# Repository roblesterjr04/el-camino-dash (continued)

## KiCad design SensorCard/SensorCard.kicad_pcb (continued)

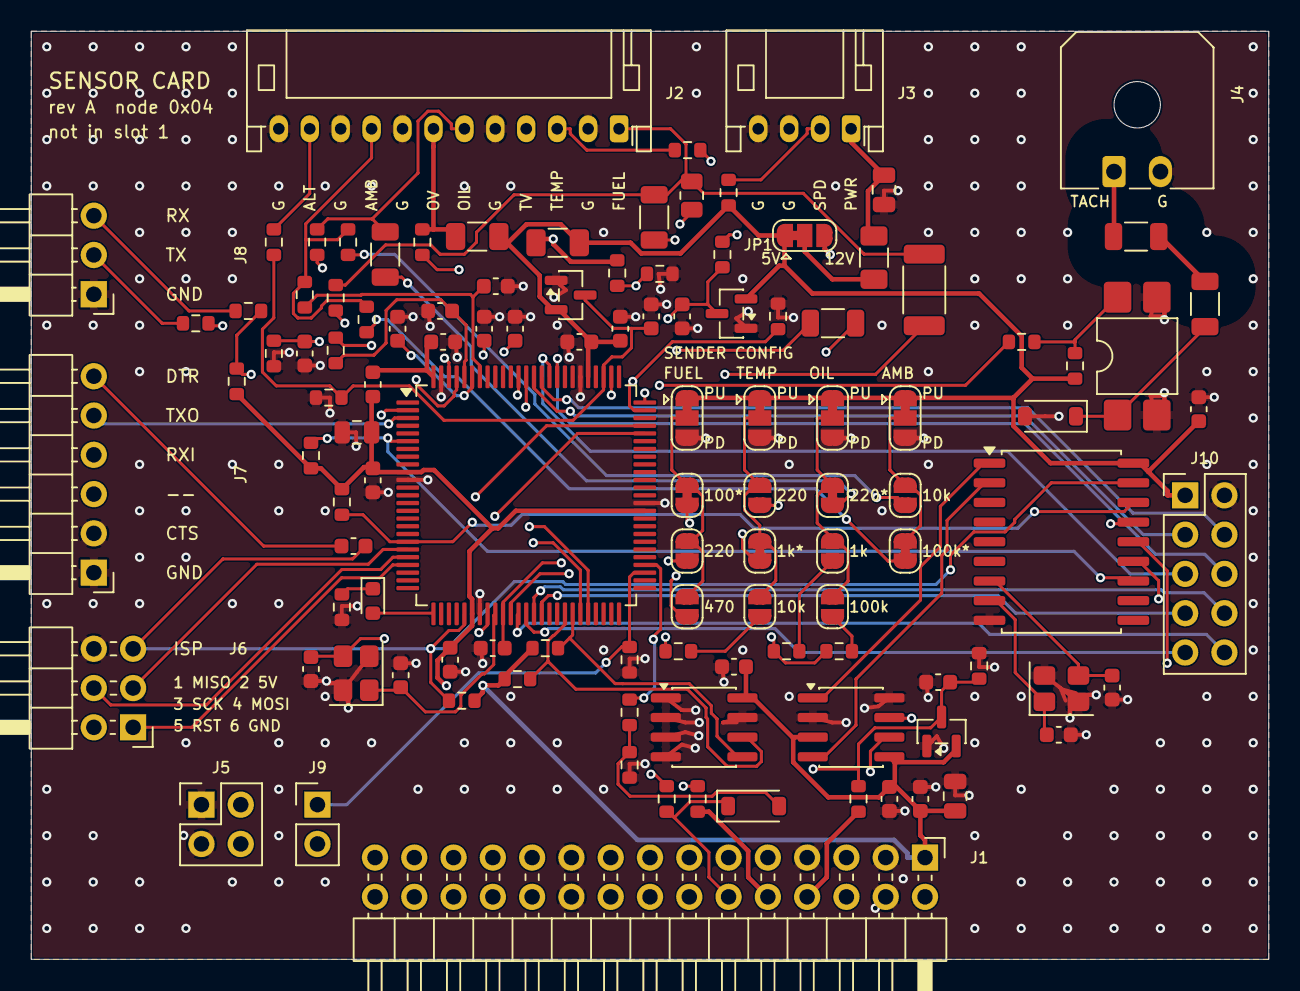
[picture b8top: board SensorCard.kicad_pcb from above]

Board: 4 copper layers, 80.0 x 60.0 mm, 114 parts (0 on the bottom side), 86 nets.

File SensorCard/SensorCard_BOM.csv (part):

Qty,Designators,Manufacturer part,Description,Package,Type,Side,Notes
1,U1,Microchip ATmega2560-16AU,"Sensor pack MCU. USART0 = FTDI header, USART1 = sensor frames (J8), SPI = MCP2515 + ISP, ICP4 / ICP5 = tach / speed",TQFP-100_14x14mm_P0.5mm,SMD,Top,Arrives blank: flash over J6 (ISP); fuses in DATASHEET.md
1,U2,Microchip MCP2515-I/SO,"CAN controller (node 0x04, fixed)",SOIC-18W_7.5x11.6mm_P1.27mm,SMD,Top,
1,U3,NXP TJA1051T/3/1J,"CAN transceiver, VIO 5 V, STBY low. No termination: a card never terminates the bus",SOIC-8_3.9x4.9mm_P1.27mm,SMD,Top,
1,U4,Fujitsu MB85RC256VPNF-G-JNERE1,"32 KB I2C FRAM, address 0x50: odometer (A / B slots with CRC-8). Lives on the card: set a new card's mileage in firmware",SOIC-8_3.9x4.9mm_P1.27mm,SMD,Top,
1,U5,Everlight EL817S1(C)(TU)-F,Tach isolation,SMDIP-4_W7.62mm,SMD,Top,LCSC C106900. Any PC817 in the 4-SMD gull wing
1,Y1,YXC X322516MOB4SI,"16 MHz, 3225, CL 12 pF (18p + 18p in series plus stray)",Crystal_SMD_3225-4Pin_3.2x2.5mm,SMD,Top,LCSC C12668. C12 / C13 18p give about 13-14 pF load (CL 12 pF part): fine
1,Y2,YXC X322516MOB4SI,"MCP2515 clock, own crystal",Crystal_SMD_3225-4Pin_3.2x2.5mm,SMD,Top,"LCSC C12668. C16 / C17 18p, as Y1"
1,J1,Sullins PRPC015DBAN-M71RC,"Right-angle 2x15 header on the bottom edge (the slot pinout, docs/hardware/accessory_ports.md). Used: 5 V, GND, CAN, switched 12 V (8), constant 12 V (10), WAKE (12). Not used: 3.3 V, slot ID (the node is fixed), LAMP, REV, I2S, audio, AUX 12 V",PinHeader_2x15_P2.54mm_Horizontal,THT,Top,"Same part as the audio and GPS cards; on the bottom edge, pins pointing off the board"
1,J2,JST S12B-PH-K-S,"Senders: 1 FUEL, 2 FUEL return, 3 ETEMP, 4 ETEMP V (5 V, 0.1 A PTC), 5 ETEMP return, 6 OILP, 7 OILP V (5 V, 0.1 A PTC), 8 OILP return, 9 AMB, 10 AMB return, 11 ALT L (alternator lamp terminal, 12 V level), 12 GND",JST_PH_S12B-PH-K_1x12_P2.00mm_Horizontal,THT,Top,
1,J3,JST S4B-PH-K-S,"Speed sensor: 1 sensor power (5 V or 12 V by JP1, 0.1 A PTC), 2 signal, 3 GND, 4 GND / shield",JST_PH_S4B-PH-K_1x04_P2.00mm_Horizontal,THT,Top,
1,J4,Molex 43650-0200,"Tach: 1 coil negative / HEI tach terminal / ignition box tach output, 2 GND",Molex_Micro-Fit_3.0_43650-0200_1x02_P3.00mm_Horizontal,THT,Top,
1,J5,XFCN PZ254V-12-4P,"RPM select jumpers (pulses per revolution; internal pull-ups): 1-2 = A, 3-4 = B",PinHeader_2x02_P2.54mm_Vertical,THT,Top,
1,J6,XFCN PZ254R-12-6P,ISP (USBasp or AVRISP mkII; USBtiny is unreliable above 128 KB). Pin 2 is the card 5 V: power the card from its slot,PinHeader_2x03_P2.54mm_Horizontal,THT,Top,
1,J7,Sullins PRPC006SBAN-M71RC,"FTDI 6-pin (5 V logic): 1 GND, 2 CTS (grounded), 3 VCC (not used: power from the slot), 4 adapter TX, 5 adapter RX, 6 DTR",PinHeader_1x06_P2.54mm_Horizontal,THT,Top,
1,J8,Sullins PREC003SBAN-M71RC,"Sensor serial (USART1, 5 V, 115200 8N1): 1 GND, 2 TX (sensor frames out: jumper wire to the main board J27 pin 1), 3 RX (in; unused in the car)",PinHeader_1x03_P2.54mm_Horizontal,THT,Top,
1,J9,Sullins PRPC002SAAN-RC,"Demo jumper: fitted = the sensor pack sends a fake sweep (bench only). 1 DEMO, 2 +5V",PinHeader_1x02_P2.54mm_Vertical,THT,Top,"Plus one 2.54 mm jumper shunt (Sullins QPC02SXGN-RC), not fitted: bench only"
1,J10,XFCN PZ254V-12-10P,"Spare 2560 pins: ADC10-13 (port K: analog or digital, pin-change interrupts), D44-D47 (PWM). 5 V logic, no protection",PinHeader_2x05_P2.54mm_Vertical,THT,Top,
1,JP1,"(PCB solder jumper, no part)",Speed sensor supply: 1-2 (bridged as delivered) = 5 V; cut 1-2 and bridge 2-3 = slot switched 12 V,SolderJumper-3_P1.3mm_Bridged12_RoundedPad1.0x1.5mm,SMD,Top,Bridged as delivered
1,JP2,"(PCB solder jumper, no part)",FUEL topology: 1-2 (bridged as delivered) = pull-up to +5 V; cut 1-2 and bridge 2-3 = pull-down to GND,SolderJumper-3_P1.3mm_Bridged12_RoundedPad1.0x1.5mm,SMD,Top,Bridged as delivered
1,JP3,"(PCB solder jumper, no part)",ETEMP topology: 1-2 (bridged as delivered) = pull-up to +5 V; cut 1-2 and bridge 2-3 = pull-down to GND,SolderJumper-3_P1.3mm_Bridged12_RoundedPad1.0x1.5mm,SMD,Top,Bridged as delivered
1,JP4,"(PCB solder jumper, no part)",OILP topology: 1-2 (bridged as delivered) = pull-up to +5 V; cut 1-2 and bridge 2-3 = pull-down to GND,SolderJumper-3_P1.3mm_Bridged12_RoundedPad1.0x1.5mm,SMD,Top,Bridged as delivered
1,JP5,"(PCB solder jumper, no part)",AMB topology: 1-2 (bridged as delivered) = pull-up to +5 V; cut 1-2 and bridge 2-3 = pull-down to GND,SolderJumper-3_P1.3mm_Bridged12_RoundedPad1.0x1.5mm,SMD,Top,Bridged as delivered
1,JP6,"(PCB solder jumper, no part)",FUEL 100 select: bridged as delivered,SolderJumper-2_P1.3mm_Bridged_RoundedPad1.0x1.5mm,SMD,Top,Bridged as delivered
1,JP7,"(PCB solder jumper, no part)",FUEL 220 select: open as delivered,SolderJumper-2_P1.3mm_Open_RoundedPad1.0x1.5mm,SMD,Top,Open as delivered
1,JP8,"(PCB solder jumper, no part)",FUEL 470 select: open as delivered,SolderJumper-2_P1.3mm_Open_RoundedPad1.0x1.5mm,SMD,Top,Open as delivered
1,JP9,"(PCB solder jumper, no part)",ETEMP 220 select: open as delivered,SolderJumper-2_P1.3mm_Open_RoundedPad1.0x1.5mm,SMD,Top,Open as delivered
1,JP10,"(PCB solder jumper, no part)",ETEMP 1k select: bridged as delivered,SolderJumper-2_P1.3mm_Bridged_RoundedPad1.0x1.5mm,SMD,Top,Bridged as delivered
1,JP11,"(PCB solder jumper, no part)",ETEMP 10k select: open as delivered,SolderJumper-2_P1.3mm_Open_RoundedPad1.0x1.5mm,SMD,Top,Open as delivered
1,JP12,"(PCB solder jumper, no part)",OILP 220 select: bridged as delivered,SolderJumper-2_P1.3mm_Bridged_RoundedPad1.0x1.5mm,SMD,Top,Bridged as delivered
1,JP13,"(PCB solder jumper, no part)",OILP 1k select: open as delivered,SolderJumper-2_P1.3mm_Open_RoundedPad1.0x1.5mm,SMD,Top,Open as delivered
1,JP14,"(PCB solder jumper, no part)",OILP 100k select: open as delivered,SolderJumper-2_P1.3mm_Open_RoundedPad1.0x1.5mm,SMD,Top,Open as delivered
1,JP15,"(PCB solder jumper, no part)",AMB 10k select: open as delivered,SolderJumper-2_P1.3mm_Open_RoundedPad1.0x1.5mm,SMD,Top,Open as delivered
1,JP16,"(PCB solder jumper, no part)",AMB 100k select: bridged as delivered,SolderJumper-2_P1.3mm_Bridged_RoundedPad1.0x1.5mm,SMD,Top,Bridged as delivered
3,D1 D4 D5,"Nexperia BAT54S,215","Input clamps to GND / 5 V (ignition sense, alternator L, speed)",SOT-23,SMD,Top,
1,D2,Vishay BAT42W-E3-08,"Hold diode: this card can only drive WAKE high, never load it (other cards drive it too)",D_SOD-123,SMD,Top,
1,D3,Lite-On LTST-C191KGKT,"Status (PB7, Arduino D13)",0603,SMD,Top,
1,D6,Diodes Inc 1N4148W-7-F,Reverse clamp across the LED (coil kickback),D_SOD-123,SMD,Top,
1,FB1,Murata BLM18KG601SN1D,AVCC filter,0603,SMD,Top,
3,F1 F2 F3,Littelfuse 1206L010/60WR,"0.1 A, 60 V feed fuses, 1206: ETEMP V, OILP V, speed sensor power",1206,SMD,Top,
1,R1,Yageo RC0603FR-0715KL,Ignition sense divider top (from the slot switched 12 V),0603,SMD,Top,
18,R2 R6 R8 R10 R11 R12 R17 R19 R21 R27 R31 R33 R34 R35 R36 R38 R39 R40,Yageo RC0603FR-0710KL,10k resistor,0603,SMD,Top,
3,R3 R30 R32,Yageo RC0603FR-07100KL,100k resistor,0603,SMD,Top,
3,R4 R37 R43,Yageo RC0603FR-0722KL,22k resistor,0603,SMD,Top,
3,R5 R13 R14,Yageo RC0603FR-074K7L,4.7k resistor,0603,SMD,Top,
1,R7,Yageo RC0603FR-0747KL,WAKE into the 2560 (series: the line may be up while the 2560 is unpowered),0603,SMD,Top,
7,R9 R16 R18 R20 R26 R29 R44,Yageo RC0603FR-071KL,1k resistor,0603,SMD,Top,
1,R15,Yageo RC0603FR-07100RL,Series R on the serial out (a wire leaves the card),0603,SMD,Top,
1,R22,Yageo RC2010FK-07100RL,"FUEL bank, 100: 0-30R senders (the factory 1964 GM sender); 2010 for 0.25 W into a shorted sender",2010,SMD,Top,Sender bias bank: selected by a solder jumper
3,R23 R25 R28,Yageo RC1206FR-07220RL,220 resistor,1206,SMD,Top,
1,R24,Yageo RC0805FR-07470RL,"FUEL bank, 470: 240-33R senders",0805,SMD,Top,Sender bias bank: selected by a solder jumper
2,R41 R42,Yageo RC1206FR-074K7L,4.7k resistor,1206,SMD,Top,
2,C1 C9,Samsung CL21B106KOQNNNE,10u capacitor,0805,SMD,Top,
14,C2 C3 C4 C5 C6 C7 C8 C10 C11 C14 C15 C18 C19 C24,Samsung CL10B104KB8NNNC,100n capacitor,0603,SMD,Top,
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
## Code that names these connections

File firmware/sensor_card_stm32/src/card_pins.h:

#pragma once

// The rev B card's pins (SensorCard2/README.md, pin map): STM32G0B1KBU6, UFQFPN-32. Names are the STM32duino port
// pin names (PA0 ...), which the generic variant defines as Arduino pin numbers.
#include <Arduino.h>
#include <stdint.h>

static const uint32_t PIN_LED = PB5;         // status LED, high = on
static const uint32_t PIN_PWR_HOLD = PA15;   // drives WAKE through D1 to hold the main board's 5 V rail
static const uint32_t PIN_RPM_SEL_A = PC6;   // J5 1-2, low = fitted (internal pull-up)
static const uint32_t PIN_RPM_SEL_B = PB3;   // J5 3-4, low = fitted (internal pull-up)
static const uint32_t PIN_TEMP_MON = PB2;    // ETEMP V feed present (10k / 15k from the 5 V feed), high = OK
static const uint32_t PIN_PRESS_MON = PB9;   // OILP V feed present, high = OK
static const uint32_t PIN_TACH = PA8;        // TIM1_CH1 (AF2), falling edge = spark (the opto pulls it low)
static const uint32_t PIN_SPEED = PB4;       // TIM3_CH1 (AF1), falling edge
static const uint32_t PIN_J8_TX = PA2;       // USART2: the sensor frames out (through U7 to 5 V)
static const uint32_t PIN_J8_RX = PA3;
static const uint32_t PIN_FRAM_SDA = PB7;    // I2C1
static const uint32_t PIN_FRAM_SCL = PB6;
// USART1 (PA9 / PA10, J7) is `Serial`: SERIAL_UART_INSTANCE / PIN_SERIAL_* in platformio.ini.
// FDCAN1 is PA11 (RX) / PA12 (TX), AF3: hw_fdcan.cpp. SWD is PA13 / PA14 (J6).

// ADC1 inputs (hw_adc.cpp scans them in this, ascending, order)
static const uint8_t ADC_FUEL = 0, ADC_TEMP = 1, ADC_OIL = 4, ADC_AMB = 5, ADC_ALT = 6, ADC_BATT = 7, ADC_WAKE = 8,
                     ADC_IGN = 9;

// The level inputs' dividers (top / bottom, kohm) and the slot voltages they switch at, the same as rev A's
static const float kIgnDivTop = 33.0f, kIgnDivBottom = 10.0f, kIgnOnVolts = 7.5f, kIgnOffVolts = 3.75f;
static const float kAltDivTop = 39.0f, kAltDivBottom = 10.0f, kAltOnVolts = 9.6f, kAltOffVolts = 4.8f;
static const float kBattDivTop = 100.0f, kBattDivBottom = 22.0f;

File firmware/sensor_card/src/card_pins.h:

#pragma once

// The sensor card's pins (SensorCard/DATASHEET.md, MCU pin map). They are the ATmega2560's pins numbered the way an
// Arduino Mega 2560 numbers them, so the same image runs on a Mega on the bench.
#include <stdint.h>

static const uint8_t PIN_CAN_CS = 53;      // PB0 (SS): MCP2515 chip select on the card
static const uint8_t PIN_CAN_INT = 2;      // PE4 (INT4): MCP2515 INT (the driver polls; it is not needed)
static const uint8_t PIN_LED = 13;         // PB7: status LED, high = on
static const uint8_t PIN_TACH = 49;        // PL0 ICP4: tach, falling edge = spark
static const uint8_t PIN_SPEED = 48;       // PL1 ICP5: speed, falling edge
static const uint8_t PIN_DEMO = 37;        // PC0: J9, high = demo sweep (10k pull-down on the card)
static const uint8_t PIN_PWR_HOLD = 36;    // PC1: drives WAKE to hold the main board's 5 V rail
static const uint8_t PIN_RPM_SEL_B = 29;   // PA7: J5 3-4, low = fitted
static const uint8_t PIN_RPM_SEL_A = 28;   // PA6: J5 1-2, low = fitted
static const uint8_t PIN_PRESS_MON = 26;   // PA4: OILP V feed monitor, high = OK
static const uint8_t PIN_TEMP_MON = 25;    // PA3: ETEMP V feed monitor, high = OK
static const uint8_t PIN_IGN = 23;         // PA1: ignition (slot switched 12 V), high = on
static const uint8_t PIN_ALT_L = 22;       // PA0: alternator L, high = charging

// ADC channels
static const uint8_t ADC_FUEL = 0, ADC_TEMP = 1, ADC_OIL = 2, ADC_AMB = 3, ADC_BATT = 8, ADC_WAKE = 9;

// MCP2515 chip-select candidates, tried in this order when none is set: the card's own, then the ones CAN shields use
static const uint8_t kCsCandidates[3] = {53, 10, 9};

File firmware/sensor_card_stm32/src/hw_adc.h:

#pragma once
#include <stdint.h>

// ADC1 scanning the eight inputs (PA0 PA1 PA4 PA5 PA6 PA7 PB0 PB1 = IN0 1 4 5 6 7 8 9) by DMA into a ring of the last
// 32 scans, hardware-oversampled 16x, so nothing ever blocks on a conversion and no interrupt runs: one scan is about
// 1.4 ms, the ring about 44 ms, and take() averages what is in it. Counts come back on rev A's 10-bit scale
// (adc_scale.h), which is what the calibration and the screens expect.
enum AdcSlot : uint8_t { SLOT_FUEL, SLOT_TEMP, SLOT_OIL, SLOT_AMB, SLOT_ALT, SLOT_BATT, SLOT_WAKE, SLOT_IGN, SLOT_COUNT };

void adc_begin();
/** The slot's average over the ring, on rev A's scale (senders and WAKE: 0..1023 ratiometric; battery: rescaled to
 *  the 5 V reference; ALT / IGN: 0..1023 of 3.3 V). False until the first scan has landed. */
bool adc_take(AdcSlot s, float *avg);
/** The latest 12-bit sample of a slot (for `adc`). */
uint16_t adc_raw12(AdcSlot s);
/** The level inputs through their dividers with hysteresis: ignition on, alternator L high. */
bool adc_ign_on();
bool adc_alt_high();

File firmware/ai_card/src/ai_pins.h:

#pragma once

// ESP32-S3-WROOM-1U-N16R8 pins on the AI card (AICard/generate/gen_sch.py is the source of truth; keep both in step).
// Not used: GPIO0 (BOOT only), 3, 45, 46 (strapping), 26-37 (flash and octal PSRAM), 19 / 20 (native USB).

#define AI_PIN_CAN_TX 9
#define AI_PIN_CAN_RX 10
#define AI_PIN_SLOT_ID 4        // ADC1_CH3: 10k to 3.3 V on the card, the slot's resistor to GND
#define AI_PIN_AUX_SENSE 5      // ADC1_CH4: AUX 12 V through 220k / 47k (2.1 V at 12 V): the buck's INPUT, since the buck waits for it
#define AI_PIN_NTC 8            // ADC1_CH7: 10k NTC (beta 3950) to GND, 10k to 3.3 V
#define AI_PIN_I2S_BCK 6        // rail BCK in (slave)
#define AI_PIN_I2S_WS 7         // rail WS in
#define AI_PIN_I2S_MIC 15       // rail MIC in (the audio card's PCM1808 data)
#define AI_PIN_I2S_RET 16       // RET data out, to the 74LVC125
#define AI_PIN_RET_OE_N 17      // 74LVC125 /OE: low = the buffer drives RET. 100k pull-up on the card: off at power-up
#define AI_PIN_LINK_TX 41       // UART1 TX -> module RXD (header pin 10), 1k in series
#define AI_PIN_LINK_RX 42       // UART1 RX <- module TXD (header pin 8), 1k in series
#define AI_PIN_BUCK_EN 11       // high enables the module's 5 V buck (NMOS pulls the buck's EN low otherwise)
#define AI_PIN_SHUTDOWN_REQ 12  // -> module header pin 31 (GPIO6), 1k in series, 100k pull-down
#define AI_PIN_ALIVE 13         // <- module header pin 29 (GPIO5), 1k in series, 100k pull-down
#define AI_PIN_ATTN 14          // spare, module header pin 33, input
#define AI_PIN_LED_MODULE 1     // green: module running
#define AI_PIN_LED_MIC 2        // amber: the microphone is open (listening)
// GPIO43 / 44 are the debug UART (J5), 19 / 20 the USB-C.

#define AI_NTC_R_FIXED 10000
#define AI_NTC_R0 10000
#define AI_NTC_BETA 3950
#define AI_AUX_PRESENT_MV 1000  // above this AUX 12 V is up (about 6.4 V at the 220k / 47k divider: 17.6 % of the input)

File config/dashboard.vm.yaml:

system:
  mode: simulation
  log_level: DEBUG
  target_fps: 30
  window_title: El Camino Dash (VM)
  display_render_mode: multi_window
  keyboard_focus_control_only: true
  startup_sweep_enabled: true
  startup_sweep_up_s: 1.1
  startup_sweep_hold_s: 0.12
  startup_sweep_down_s: 0.7
  left_to_right_preview: false
  left_to_right_spacing_px: 16
  menu_schema_path: config/menu_schema.yaml
  odometer_start_miles: 12345.0
  odometer_persist_enabled: true
  odometer_state_path: data/odometer_state.vm.json
  odometer_write_interval_s: 1.5
  map_view_visible: false
  map_display_id: gauge_right
  simulation_map_image_path: assets/maps/testmap.png
  # Keep VM theme pinned unless manually changed in config.
  theme_persist_enabled: false
  theme_state_path: data/theme_state.vm.json
  raw_input_log_enabled: true
  raw_input_log_path: data/raw_inputs.vm.log
  raw_input_log_interval_s: 0.2

displays:
  - id: gauge_left
    enabled: true
    shape: round
    width: 1080
    height: 1080
    position: [0, 0]
    monitor_index: 0
    windowed: true
    fullscreen: false
    fps: 30
    role: gauge
    gauge_id: speedometer
  - id: gauge_center
    enabled: true
    shape: round
    width: 720
    height: 720
    position: [1080, 0]
    monitor_index: 1
    windowed: true
    fullscreen: false
    fps: 30
    role: gauge
    gauge_id: fuel
  - id: gauge_right
    enabled: true
    shape: round
    width: 1080
    height: 1080
    position: [540, 0]
    monitor_index: 2
    windowed: true
    fullscreen: false
    fps: 30
    role: gauge
    gauge_id: tachometer
  - id: control_rect
    enabled: true
    shape: rectangle
    width: 1050
    height: 600
    position: [0, 540]
    monitor_index: 3
    windowed: true
    fullscreen: false
    fps: 30
    role: control

themes:
  active: default
  allow_fallback: true
  theme_root: themes
  gauge_asset_root: assets/gauges
  font_name: freesansbold.ttf

gauges:
  speedometer: {label: Speed, unit: mph, source: speed_sensor.vehicle_speed, min_value: 0, max_value: 140, smoothing_alpha: 0.2, odometer_source: vehicle.odometer_miles, odometer_label: ODO, odometer_unit: mi, odometer_decimals: 1}
  tachometer: {label: RPM, unit: rpm, source: analog_inputs.engine_rpm, min_value: 0, max_value: 6000, smoothing_alpha: 0.2, secondary_label: Temp, secondary_source: analog_inputs.coolant_temp, secondary_unit: "F"}
  tsps: {label: TSPS, unit: "%", source: analog_inputs.fuel_level, min_value: 0, max_value: 100, smoothing_alpha: 0.3}
  fuel: {label: Fuel, unit: "%", source: analog_inputs.fuel_level, min_value: 0, max_value: 100, smoothing_alpha: 0.3}
  temp: {label: Temp, unit: "F", source: analog_inputs.coolant_temp, min_value: 40, max_value: 250, smoothing_alpha: 0.2}
  amp: {label: Amp, unit: A, source: analog_inputs.system_amp, min_value: -100, max_value: 100, smoothing_alpha: 0.2}
  oil: {label: Oil, unit: "psi", source: analog_inputs.oil_pressure, min_value: 0, max_value: 60, smoothing_alpha: 0.3}

inputs:
  rotary_encoders:
    - {id: menu, enabled: false, pin_a: 17, pin_b: 27, pin_button: 22, pull_up: true, debounce_ms: 3, invert_direction: false, acceleration: 1.0}
    - {id: aux, enabled: false, pin_a: 23, pin_b: 24, pin_button: 25, pull_up: true, debounce_ms: 3, invert_direction: false, acceleration: 1.0}
  analog_inputs:
    - {id: engine_rpm, enabled: false, adc_type: mcp3008, spi_bus: 0, spi_device: 0, channel: 0, min_raw: 0, max_raw: 1023, scale_min: 0, scale_max: 8000}
    - {id: fuel_level, enabled: false, adc_type: mcp3008, spi_bus: 0, spi_device: 0, channel: 1, min_raw: 0, max_raw: 1023, scale_min: 0, scale_max: 100}
    - {id: coolant_temp, enabled: false, adc_type: mcp3008, spi_bus: 0, spi_device: 0, channel: 2, min_raw: 0, max_raw: 1023, scale_min: 100, scale_max: 260}
    - {id: system_amp, enabled: false, adc_type: mcp3008, spi_bus: 0, spi_device: 0, channel: 3, min_raw: 0, max_raw: 1023, scale_min: -100, scale_max: 100}
  speed_sensors:
    - {id: vehicle_speed, enabled: false, gpio_pin: 5, pulses_per_revolution: 20, wheel_circumference_m: 2.1, timeout_ms: 800, smoothing_alpha: 0.35}
  simulated_data:
    enabled: false
    speed_period_s: 8.0
    rpm_period_s: 3.0
    fuel_period_s: 24.0
    temp_period_s: 14.0
    amp_period_s: 5.0
    oil_period_s: 9.0
    speed_range: [0, 95]
    rpm_range: [800, 6000]
    fuel_range: [0, 100]
    temp_range: [40, 250]
    amp_range: [-35, 60]
    oil_range: [8, 62]
  keyboard_sim:
    enabled: true
    rotate_repeat_ms: 130
    rpm_max: 10000
    temp_min: 40
    temp_max: 250
    amp_min: -100
    amp_max: 100
    oil_min: 0
    oil_max: 60
    mappings:
      menu_rotate_left: K_LEFT
      menu_rotate_right: K_RIGHT
      menu_press: K_RETURN
      aux_rotate_left: K_COMMA
      aux_rotate_right: K_PERIOD
      aux_press: K_SLASH
      speed_up: K_w
      speed_down: K_s
      rpm_up: K_e
      rpm_down: K_d
      fuel_up: K_r
      fuel_down: K_f
      temp_up: K_t
      temp_down: K_g
      amp_up: K_y
      amp_down: K_h
      oil_up: K_u
      oil_down: K_j

integrations:
  navit: {enabled: false, executable: navit, args: []}
  media: {enabled: false, music_root: media, startup_track: "", startup_volume: 0.5}
  bluetooth_metadata: {enabled: false, provider: mock}

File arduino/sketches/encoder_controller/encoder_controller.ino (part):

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// - UART1 TX=GP0, RX=GP1 (Pi link @115200)
// - SPI0 SCK=GP18, MOSI=GP19, MISO=GP16
static const uint8_t PIN_IR_RECEIVE = 22;
static const uint8_t OLED_CS = 17;
static const uint8_t OLED_DC = 20;
static const uint8_t OLED_RST = 21;
static const uint8_t UART_TX_PIN = 0;
static const uint8_t UART_RX_PIN = 1;
static const uint8_t OLED_SPI_SCK = 18;
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// IR demodulator OUT (active-low bursts; module usually has weak pull-up). Analog pin as digital in.
static const uint8_t PIN_IR_RECEIVE = A0;
// --- SPI OLED (SSD1322 256x64). HW SPI: MOSI=11, SCK=13 ---
static const uint8_t OLED_CS = 10;
// DC must go to the module's D/C pin; do not swap with RST — wrong wiring shows snow/garbage.
static const uint8_t OLED_DC = A4;
static const uint8_t OLED_RST = A5;
#define ELC_LINK_SERIAL Serial
#endif

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}

static void pulseOledReset() {
  pinMode(OLED_RST, OUTPUT);
  digitalWrite(OLED_RST, LOW);
  delay(10);
  digitalWrite(OLED_RST, HIGH);
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  SPI.setRX(OLED_SPI_MISO);
#endif
  SPI.begin();
  pinMode(OLED_CS, OUTPUT);
  digitalWrite(OLED_CS, HIGH);
  pinMode(OLED_DC, OUTPUT);
  pulseOledReset();

  linkBothPrint(F("OLED driver: "));
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
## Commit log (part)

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2026-02-27 Update README and configuration files for enhanced display mode support and installation scripts
    - Updated README.md to include detailed instructions for VM and hardware display modes, including new scripts for running in different environments.
    - Modified dashboard.dev.yaml and dashboard.vehicle.yaml to include new display settings such as `monitor_index`, `windowed`, and `fullscreen`.
    - Enhanced install_app.sh and install_pi_base.sh scripts to support virtual environment creation and installation with Xvfb.
    - Added new command-line arguments for display and render modes in main.py.
    - Improved error handling and configuration validation in the application.
    - Updated input manager to manage
2026-03-02 Refactor configuration and remove VM support scripts
    - Updated README.md to reflect changes in display definitions and removed references to VM-specific configurations.
    - Removed dashboard.vm.yaml and associated scripts for VM autostart and Xvfb support.
    - Adjusted dashboard.dev.yaml and dashboard.vehicle.yaml to streamline display settings, including the removal of the control display.
    - Enhanced main.py to support headless operation and updated display mode handling.
    - Improved validation in config.py to enforce display role requirements and added support for SPI display configurations.
    - Updated input management and signal handling in app.py for better shutdown behavior.
2026-03-02 Enhance installation script and configuration for display modes
    - Updated install.sh to include command-line options for skipping package installation and syncing, as well as specifying display modes and boot splash settings.
    - Added support for SPI and HDMI service files, improving flexibility for different display configurations.
    - Enhanced README.md with detailed installation steps for HDMI display setup and Bluetooth audio integration.
    - Updated requirements.txt to conditionally include RPi.GPIO and spidev for ARM platforms.
    - Improved validation in config.py to support new Bluetooth audio settings and turn signal configurations.
    - Refactored input handling in keyboard_sim.py to manage t
2026-03-04 Enhance installation script and configuration for Arduino integration
    - Updated install.sh to include new command-line options for Arduino firmware compilation and upload, allowing for better integration with Arduino devices.
    - Added functions for detecting Arduino serial ports and managing Arduino settings, including baud rate and GPIO configurations.
    - Enhanced README.md with instructions for Arduino sketch setup and flashing process.
    - Updated requirements.txt to include additional dependencies for Arduino communication.
    - Improved validation in config.py to support new Arduino serial configurations and fault simulation settings.
    - Refactored app.py to manage Arduino fault states and inte
2026-03-16 Archive legacy installation scripts and transition to image-first provisioning
    - Updated install.sh to inform users of the new image-first workflow using rpi-image-gen, removing legacy install logic.
    - Enhanced README.md to reflect the new provisioning process and updated deployment instructions for day-to-day development.
    - Added support for IR protocol configuration in dashboard YAML files, allowing for better integration with IR remote controls.
    - Improved deploy_to_pi.sh with new command-line options for service management and Python dependency updates.
    - Refactored configuration validation in config.py to support new IR remote settings.
    - Various updates to dashboard configuration files
2026-03-17 Update configuration and code for improved functionality and organization
    - Added new ambient temperature thermistor support in sensor_pack.ino, including pin definitions and reading logic.
    - Enhanced Arduino serial communication with a handshake mechanism to improve reliability.
    - Updated gauge-cluster-hdmi.service to streamline service startup and removed unnecessary dependencies on graphical targets.
    - Refined power_control_listener.py to include a startup ignore period for more stable operation during boot.
    - Adjusted dashboard configuration files to reflect changes in device layers and user permissions.
    - Improved installation scripts to support new command-line options and configuratio
2026-03-19 Update installation scripts and configuration for improved logging and Arduino integration
    - Enhanced install.sh to include detailed logging for service starts and errors, improving troubleshooting capabilities.
    - Updated Arduino serial port configurations across multiple dashboard YAML files to use /dev/ttyAMA3 for consistency.
    - Added new user group permissions in install.sh to ensure proper access for input devices.
    - Improved README.md with additional details on raw scancode mapping for IR remotes.
    - Refined wiring pinout documentation to clarify changes in UART and SPI configurations.
    - Various updates to ensure better integration and performance across the dashboard application.
2026-03-19 Update systemd installation script to manage gauge-power-control service
    - Added symlink for gauge-power-control.service to multi-user.target.wants.
    - Removed unnecessary cleanup of gauge-power-control.service from graphical targets.
    - Simplified comments regarding the power-control unit's default disabled state.
    - Ensured proper organization of service files for improved systemd management.
2026-03-23 Refactor wiring pinout and configuration for improved Arduino integration
    - Updated wiring pinout documentation to reflect changes in I2C and UART configurations for sensor-pack and encoder Arduino.
    - Disabled MCP23017 controls in dashboard configuration files, transitioning to dedicated encoder Arduino serial input.
    - Standardized serial port paths across multiple dashboard YAML files to use /dev/serial0 and /dev/ttyAMA4.
    - Enhanced installation scripts to support new command-line options for Arduino firmware management and improved logging.
    - Introduced new menu options for Wi-Fi management in menu schema, enhancing user interface functionality.
    - Various updates to ensure better integrati
2026-03-23 Remove legacy install.sh script and update documentation for new image-first workflow
    - Deleted the install.sh script as the project transitions to an image-first workflow using rpi-image-gen.
    - Updated WIRING_PINOUT.md to reflect changes in wiring configurations for IR and UART connections.
    - Enhanced Arduino-related documentation in README.md to include new installation and upload scripts.
    - Improved compile and upload scripts for Arduino to ensure better integration and functionality.
    - Updated dashboard configuration files to align with the new architecture and remove deprecated settings.
    - Various improvements to ensure consistency and clarity across documentation and configuration file
2026-04-01 Update wiring and configuration for improved Arduino integration and documentation
    - Added freetype-py to requirements.txt for enhanced font rendering.
    - Updated WIRING_PINOUT.md to clarify HDMI-first vehicle UI and UART connections for encoder and sensor pack.
    - Refined Arduino-related documentation in README.md to include new installation and upload scripts for RP2040.
    - Standardized serial port paths in dashboard configuration files to use /dev/ttyAMA1 and /dev/ttyAMA4.
    - Adjusted dashboard YAML files to disable legacy I2C configurations and enable Arduino serial communication.
    - Enhanced menu schema to include new options for Bluetooth and improved user interface functionality.
2026-04-01 HDMI: dual-head X11 extended option, Pi image hooks, hdmi5 layout
    - Boot: per-HDMI [HDMI:0]/[HDMI:1] timings; drop kernel video= force
    - hdmi5: single_window KMS path; optional fourth gauge for X11 span (x=2880)
    - DisplayManager: 180° view flip, multi-window error handling, traceback on init fail
    - X11 extended: x11-configure-extended-desktop.sh, start-gauge-hdmi-x11-extended.sh
    - Systemd: gauge-cluster-hdmi-x11-extended.service; Conflicts with kms unit
    - Manifest + install hooks for new scripts; config validation display_rotation_deg
2026-04-01 Add HDMI diagnostics and second-output test helpers (DRM, kmscube, pygame+X11)
    Made-with: Cursor
2026-04-01 test_hdmi_pygame_x11: add --only N for second display flash
    Made-with: Cursor
2026-04-01 test_hdmi_pygame_x11: document --only in docstring
    Made-with: Cursor
2026-04-01 Fix 4in dash: fourth gauge x=2160, xinit as root for Xorg, x11 client script
    - RandR desktop is 2160+720 wide; fourth gauge at 2880 was off-screen
    - gauge-cluster-hdmi-x11-extended: run start script as root (not pi) so Xorg can open vt1
    - Split x11-extended-xinit-client.sh: xrandr then runuser pi for pygame
    Made-with: Cursor
2026-04-22 Enhance ambient illumination and backlight control for ESP32-P4
    - Added support for ambient illumination via GPIO 24, allowing for dimming based on vehicle signals.
    - Updated backlight control to use GPIO 26 with PWM, ensuring compatibility with various display setups.
    - Introduced new functions for managing backlight levels and illumination polling in the display setup.
    - Updated documentation in WIRING_PINOUT.md to reflect these changes and clarify GPIO usage.
    This update improves user experience by providing better control over display brightness and ambient lighting conditions.
